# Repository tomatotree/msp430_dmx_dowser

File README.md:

This project implements a DMX controlled projector dowser using a MSP430 MCU and a hobby servo.  

Currently the code is functional, and has been tested using a Launchpad and a HiTec 5010 Servo.  

TODO:
* Finalize PCB Layout
* Add support for DMX channel selection via LCD screen and buttons.

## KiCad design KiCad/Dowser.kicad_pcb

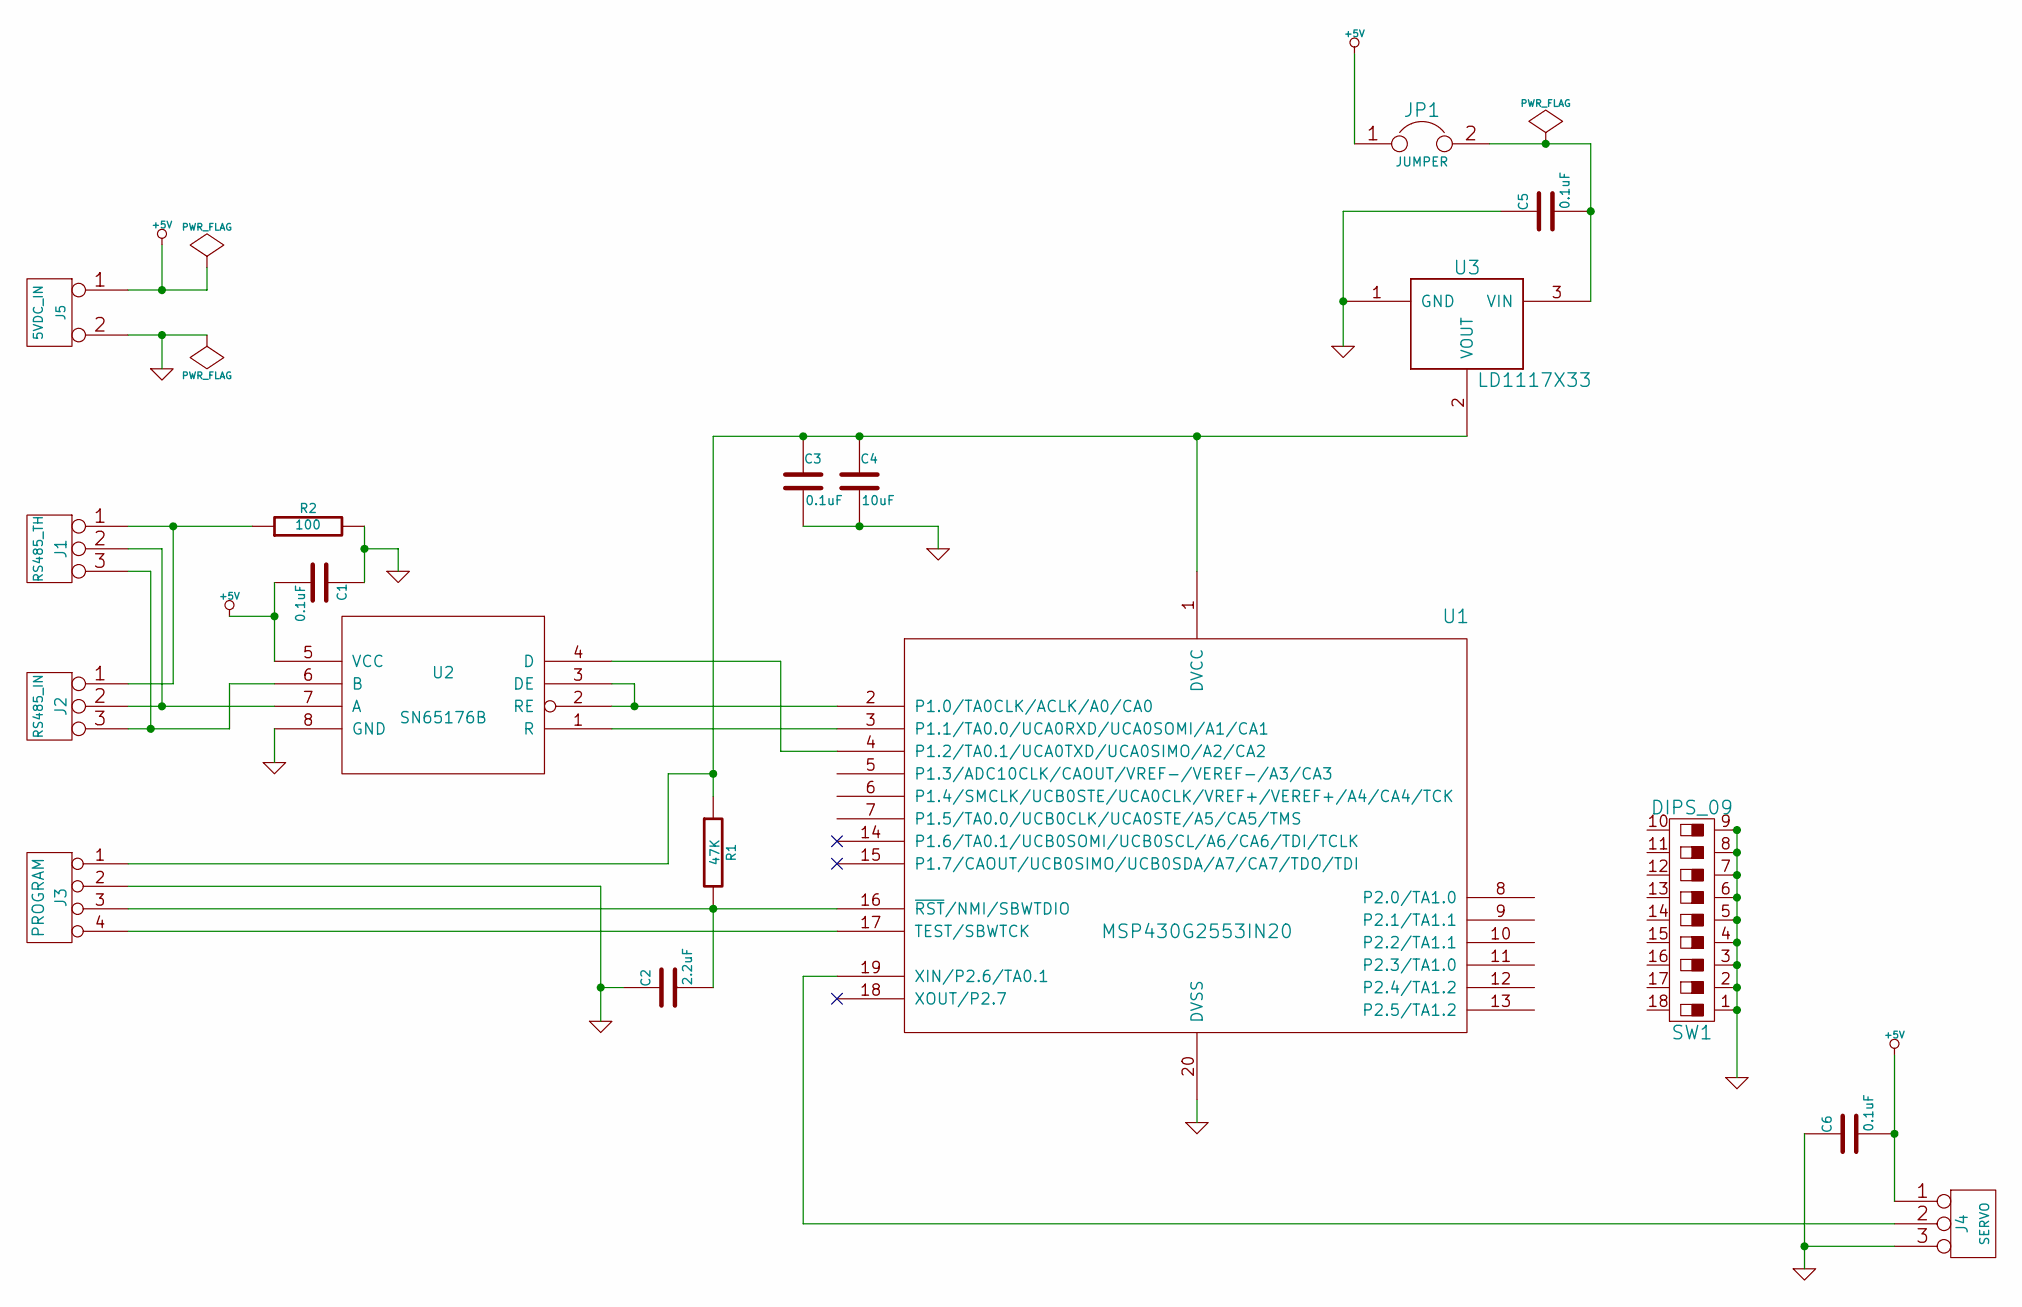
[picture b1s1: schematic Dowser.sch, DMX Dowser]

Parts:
C1, C3, C5, C6: 0.1uF
C2: 2.2uF
C4: 10uF
J1: RS485_TH
J2: RS485_IN
J3: PROGRAM
J4: SERVO
J5: 5VDC_IN
JP1: JUMPER
R1: 47K
R2: 100
SW1: DIPS_09
U1: MSP430G2553IN20
U2: SN65176B; MODULE
U3: LD1117X33

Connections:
+5V: C1.2, C6.2, J4.1, J5.1, JP1.1, U2.5 (VCC)
GND: C1.1, C2.1, C3.2, C4.2, C5.1, C6.1, J3.2, J4.3, J5.2 (PM), R2.2, SW1.1, SW1.2, SW1.3, SW1.4, SW1.5, SW1.6, SW1.7, SW1.8, SW1.9, U1.20 (DVSS), U2.8 (GND), U3.1 (GND)
unnamed: U1.3 (P1.1/TA0.0/UCA0RXD/UCA0SOMI/A1/CA1), U2.1 (R)
unnamed: J3.4, U1.17 (TEST/SBWTCK)
unnamed: J4.2 (PM), U1.19 (XIN/P2.6/TA0.1)
unnamed: J1.1, J2.1, R2.1
unnamed: C2.2, J3.3, R1.2, U1.16 (~RST~/NMI/SBWTDIO)
unnamed: C5.2, JP1.2, U3.3 (VIN)
unnamed: J1.2 (PM), J2.2 (PM), U2.7 (A)
unnamed: J1.3, J2.3, U2.6 (B)
unnamed: U1.2 (P1.0/TA0CLK/ACLK/A0/CA0), U2.2 (RE), U2.3 (DE)
unnamed: U1.4 (P1.2/TA0.1/UCA0TXD/UCA0SIMO/A2/CA2), U2.4 (D)
unnamed: C3.1, C4.1, J3.1, R1.1, U1.1 (DVCC), U3.2 (VOUT)

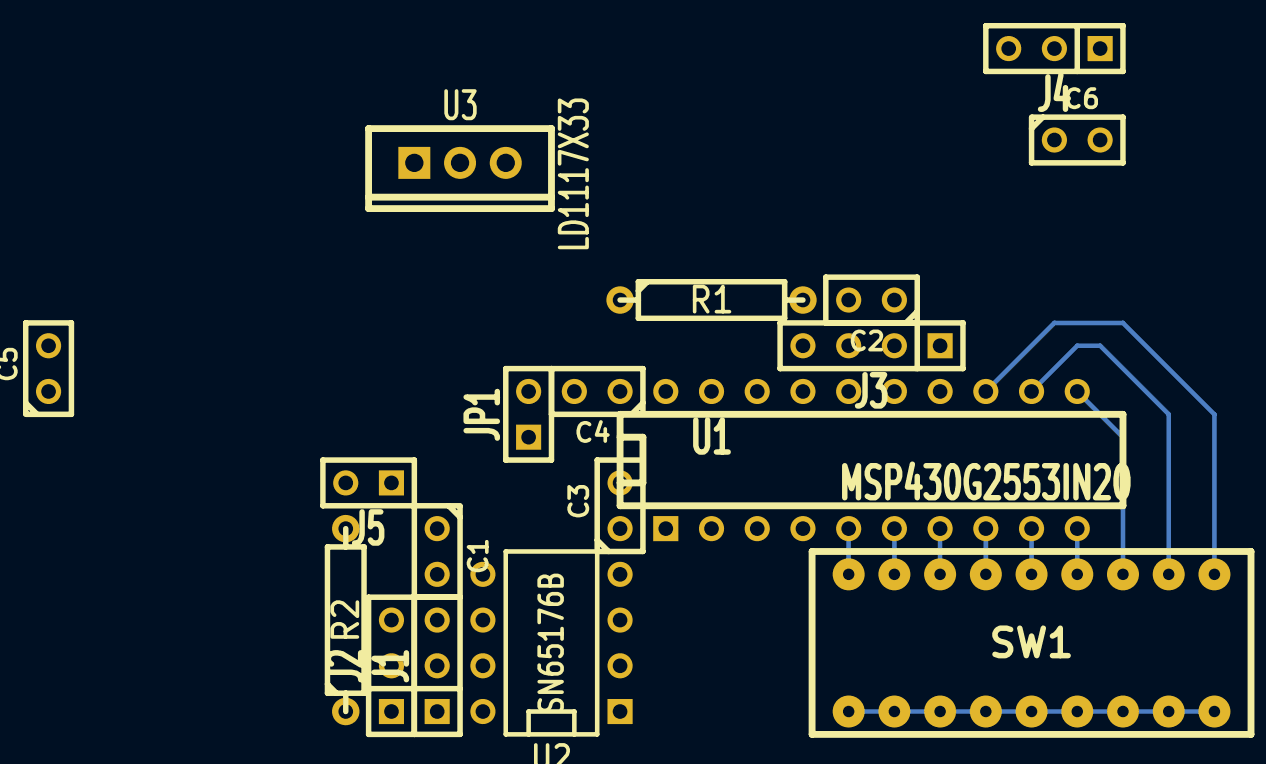
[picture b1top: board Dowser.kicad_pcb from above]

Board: 2 copper layers, 18 parts (0 on the bottom side), 13 nets.

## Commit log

2014-09-06 Added readme file, KiCad schematic and partial (unfinished) board layout.
